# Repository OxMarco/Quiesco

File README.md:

<div align="center">

<picture>
  <source media="(prefers-color-scheme: dark)" srcset=".github/assets/banner-dark.svg">
  
</picture>

<br><br>

<br>

**[Build your own](#-build-your-own)** · **[Hardware](hardware/)** · **[Firmware](firmware/)** · **[App](app/)**

</div>

---

Quiesco is a pocket-sized monitor made for the room you sleep in. It measures
**CO₂, temperature, humidity, light and noise**, shows them on an e-ink screen
that reads from across the room, and syncs every night straight to your
phone. There is no Wi-Fi, no cloud and no account: your data stays yours.

Everything is open. This repository holds the PCB, the case, the firmware and
the companion app, so you can build one from scratch, reflash it from the
Arduino toolchain, or take it apart and make it your own.

Quiesco is a product of [Impossible Labs](https://impossiblelabs.xyz).

<picture>
  <source media="(prefers-color-scheme: dark)" srcset=".github/assets/screens-dark.svg">
  
</picture>

## Contents

- [Why Quiesco](#-why-quiesco)
- [What it measures](#-what-it-measures)
- [How it works](#-how-it-works)
- [Specs](#-specs)
- [Build your own](#-build-your-own)
- [Upgrade firmware](#-upgrade-firmware)
- [Repository map](#-repository-map)
- [Roadmap](#-roadmap)
- [The story behind it](#-the-story-behind-it)
- [Contributing](#-contributing)
- [Licence](#-licence)

## 🌙 Why Quiesco

Environmental monitors have boomed: Aranet, Airvalent and friends made CO₂
tracking friendly. But they are general-purpose. They watch the air, and
little else, against office standards.

Quiesco is built for the **bedroom**. Light and noise matter as much as CO₂ and
temperature for a good night, so it measures all of them and judges each one
against a comfort band. Every reading is **actionable**:

| When it says… | …you can |
|---|---|
| CO₂ is high | open a window or run ventilation |
| too warm, too cold | adjust heating, cooling or bedding |
| too dry, too damp | humidify or dehumidify |
| too much light | close the blinds or wear a sleep mask |
| too loud | check the insulation or reach for earplugs |

And unlike commercial devices, it is **completely open and unlocked**: it runs
the Arduino bootloader, so you can change the firmware with the Arduino IDE or
your favourite editor.

## 📊 What it measures

| Reading | Sensor | Comfortable | Warn | Bad |
|---|---|---|---|---|
| CO₂ | Sensirion **SCD41** (photoacoustic NDIR) | ≤ 800 ppm | 800–1000 ppm | > 1000 ppm |
| Temperature | Bosch **BME280** | 16–20 °C | 14–16 · 20–24 °C | < 14 · > 24 °C |
| Humidity | Bosch **BME280** | 40–60 % | 30–40 · 60–70 % | < 30 · > 70 % |
| Noise | Knowles **SPH0641LU4H-1** PDM mic, dB(A) Leq over ~7 s | ≤ 45 dB | 45–55 dB | > 55 dB |
| Light | Vishay **VEML7700** | informational | | |
| Pressure | Bosch **BME280** | informational; also compensates CO₂ | | |

The same bands drive the e-ink screen and the app, so the phone and the panel
always agree. The full policy is in [`firmware/UI.md`](firmware/UI.md#3-comfort-bands).

> [!IMPORTANT]
> Keep the unit out of direct sunlight. Sun on the case heats the sensors, so
> temperature reads several degrees high and humidity reads low. On a test
> bench, afternoon sun pushed the reading to 36 °C. A shaded bedside table or
> shelf, away from radiators and air vents, gives readings you can trust.

## ⚙ How it works

```mermaid
flowchart LR
    subgraph unit["Quiesco unit · nRF52840"]
        direction TB
        rail["Switched sensor rail"] --> sensors["SCD41 · BME280<br/>VEML7700 · PDM mic"]
        sensors --> cycle["Measurement cycle"]
        cycle --> flash[("8 MB flash<br/>sample log")]
        cycle --> eink["1.54″ e-ink<br/>Face · Ledger · Bento"]
        cycle --> ble["BLE service"]
        flash --> ble
    end
    ble <-- "authenticated, enrolled over USB" --> app["Companion app<br/>iOS · Android"]
    app --> db[("SQLite<br/>on your phone")]
```

Every interval (1, 5, 10 or 30 minutes; default **5 minutes**) the unit powers
up its sensor rail, measures everything, applies your calibration offsets,
appends the reading to its on-board log, redraws the e-ink panel only if the
picture changed, then powers the rail down and sleeps. A sensor that fails is
reported as unavailable, and the cycle carries on without it.

The app enrols with a unit while it is on USB power, using a six-digit code
shown on the panel. After that it sets the clock, downloads the log, charts
each night and lets you pick the screen or calibrate the sensors. One phone
can hold several units, each with its own name and sleep window.

## 📐 Specs

| | |
|---|---|
| **MCU** | Nordic nRF52840 on a Seeed XIAO nRF52840 Plus module, Arduino bootloader |
| **Connectivity** | Direct to the phone over the nRF52840's Bluetooth LE radio; only an enrolled phone can read data or change settings |
| **Sensors** | CO₂, temperature, humidity, pressure, light, noise |
| **Display** | GoodDisplay GDEW0154T8D, 1.54″ 152 × 152 e-ink, holds its image unpowered |
| **Storage** | Winbond W25Q64 8 MB SPI NOR flash (config + sample log) |
| **Power** | 3.7 V ~400 mAh LiPo (453035), USB-C charging, switched peripheral rail |
| **Expansion** | JST I²C and UART headers |
| **Case** | Two-part enclosure, MJF-printed in black PA12 nylon, four M3 screws ([why nylon](hardware/README.md#material)) |

## 🛠 Build your own

A Quiesco takes an afternoon to put together once the parts arrive. Each step
links to the folder with the details.

### What you need

- The **PCBA**: the board from [`hardware/`](hardware/), ordered assembled
- A **GDEW0154T8D** 1.54″ e-ink panel (24-pin FPC)
- A **3.7 V LiPo** that matches your board's battery connector: a ~400 mAh 453035
  (4.5 × 30 × 35 mm) with a **JST SH 1.0 2-pin** lead for the JST SH board, or
  the certified **EEMB LP402535-PCM-PTC-LD/-A22852** for the Minitek board (see
  [`hardware/`](hardware/README.md))
- A **3D-printed case** (MJF PA12 nylon, dyed black) and **4 × M3×10 socket-head screws**
- A USB-C cable, a Mac or Linux machine, and a phone with Bluetooth

### Steps

Start by cloning the repository:

```sh
git clone https://github.com/OxMarco/Quiesco.git
cd Quiesco
```

1. **Order the board** → [`hardware/`](hardware/README.md#order-the-board)
   Send the Gerbers, BOM and pick-and-place files to a PCB assembly service.
2. **Print the case** → [`hardware/`](hardware/README.md#print-the-case)
   The STL is ready to slice; STEP files are there if you want to modify it.
3. **Assemble** → [`hardware/`](hardware/README.md#assemble)
   Seat the display, plug in the battery, close the case.
4. **Test the unit** → [`TESTING.md`](TESTING.md)
   Copy the factory test onto the unit and check its screen says `PASS`.
5. **Flash the firmware** → [`firmware/`](firmware/README.md#quick-start)
   `make build`, then upload over USB.
6. **Install the app** → [`app/`](app/README.md#run-it)
   Build it onto your phone, plug the unit into USB and pair.

## ⬆ Upgrade firmware

No software needed, on macOS, Windows or Linux. Plug the unit into a
computer, tap **Settings → your unit → Update firmware** in the app, and a drive called
`XIAO-BOOT` appears. Copy `quiesco-X.Y.Z.uf2` onto it, and the unit restarts
with the new firmware. Settings, enrolled phones, calibration and history
are kept.

Troubleshooting, units without the app option, and making a release:
[`AGENT.md`](AGENT.md).

## 🗺 Repository map

| Folder | What's inside | Read this |
|---|---|---|
| [`hardware/`](hardware/) | Altium sources, schematic PDF, Gerbers, BOM, pick-and-place, case STL/STEP | [hardware/README.md](hardware/README.md) |
| [`firmware/`](firmware/) | Arduino C++ firmware for the nRF52840, test sketches, host tests and tools | [firmware/README.md](firmware/README.md) |
| [`app/`](app/) | Expo / React Native companion app for iOS and Android | [app/README.md](app/README.md) |
| [`landing/`](landing/) | The [quiesco.rest](https://quiesco.rest) website (Astro) | [landing/README.md](landing/README.md) |

Going deeper:

- [`firmware/HARDWARE.md`](firmware/HARDWARE.md): the board as the firmware sees it, pin map, traps and debugging
- [`firmware/SOFTWARE.md`](firmware/SOFTWARE.md): firmware architecture and features
- [`firmware/UI.md`](firmware/UI.md): the e-ink screens, pixel by pixel
- [`firmware/src/protocol/PROTOCOL.md`](firmware/src/protocol/PROTOCOL.md): the BLE contract between unit and app
- [`TESTING.md`](TESTING.md): testing each assembled unit, for builders and manufacturers
- [`TEST-PLAN.md`](TEST-PLAN.md): how the app and firmware are tested in code and CI
- [`AGENT.md`](AGENT.md): updating a unit's firmware (copy a file onto its USB drive)

## 🧭 Roadmap

- [x] PCB v1, assembled and tested
- [x] Measurement cycle with all sensors, calibration and CO₂ forced recalibration
- [x] E-ink screens: Face, Ledger and Bento
- [x] Persistent sample log on the on-board flash
- [x] BLE protocol with phone enrolment and authentication
- [x] Companion app: live reading, night charts, calibration
- [ ] BLE tested on air: iPhone and Mac done (2026-10-07), Android still to test
- [x] Firmware updates over USB, started from the app: copy one file, no software ([`AGENT.md`](AGENT.md))
- [ ] Measured power budget and battery life
- [x] App: more than one unit per phone, each with its own name and sleep window
- [ ] App on the App Store and Google Play
- [ ] Units for sale — *coming soon*
- [ ] Later: Quiesco XL, with PM2.5, PM10 and more sensors for fuller air-quality control, and a bigger screen

## 📖 The story behind it

<details>
<summary>Why I built Quiesco</summary>

<br>

Despite having studied electrical engineering and physics, I never had the
chance to work on electronics outside of university. My main job for the past
few years has been in fintech, mostly on software architecture. Yet I have
always wanted to launch my own product.

I own an Airvalent and a couple of Xiaomi environmental sensors and had a
chance to review the Aranet too, yet I felt these little devices could
definitely do more. That's why, in early 2026, I decided to dedicate part of my
free time to building Quiesco from the ground up.

The choice of sensors was tough. There are clear contenders on the market, but
most come with obvious drawbacks, like relying on the BME280's self-heating
element for the primary temperature reading, or gas sensors that draw too much
current for a rather generic value like VOC. So temperature, humidity and pressure
come from a BME280 on the switched rail, never self-heated, and the SCD41 is
used for CO₂ only.

**I wanted data that is actionable:** high CO₂ → ventilate; too much light →
wear a sleep mask; too much noise → check the acoustic insulation or use
earplugs.

</details>

## 🤝 Contributing

Issues and pull requests are welcome, from a typo to a new screen.

- **Firmware:** run `make verify` in `firmware/` before opening a PR; it checks
  the source policy and runs the host tests.
- **App:** run `npm test`, `npx tsc --noEmit` and `npx expo lint` in `app/`.
- **Protocol:** a change to the BLE contract touches both sides. Update
  [`PROTOCOL.md`](firmware/src/protocol/PROTOCOL.md), the firmware codec and
  the app's `src/protocol/` together; the golden vectors keep them honest.

## 🙏 Acknowledgements

Many thanks to the engineers at **PCBWay**, who helped tailor the PCB and the
enclosure to production standards.

## 📜 Licence

Quiesco is free and open source under the [GNU General Public License v3.0](LICENSE).
Third-party components are listed in
[`firmware/THIRD_PARTY_NOTICES.md`](firmware/THIRD_PARTY_NOTICES.md).

<div align="center">
<br>
<sub>Quiesco is a product of <a href="https://impossiblelabs.xyz">Impossible Labs</a> · <a href="https://quiesco.rest">quiesco.rest</a></sub>
</div>

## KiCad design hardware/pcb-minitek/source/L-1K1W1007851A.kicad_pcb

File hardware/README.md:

# Quiesco hardware

Everything you need to manufacture a Quiesco unit: the PCB **v1**
(`L-1K1W1007851A`) design and factory files, and the 3D-printable enclosure.

PCB v1 comes in two versions. They are the same board except for the battery
connector, J2. Each version has its own folder, and the two sets of files
must not be mixed.

| Version | Folder | J2, battery connector | Battery that plugs in | Design tool |
|---|---|---|---|---|
| **JST SH** | [`pcb-jst-sh/`](pcb-jst-sh/) | JST **SM02B-SRSS-TB**, SH 1.0 mm, 2-pin | any 453035-size LiPo with a JST SH 1.0 lead | Altium |
| **Minitek** | [`pcb-minitek/`](pcb-minitek/) | Amphenol **10144041-02011LF**, Minitek 0.8 mm, 2-pin | EEMB **LP402535-PCM-PTC-LD/-A22852**, IEC 62133-2 certified, used as supplied | KiCad |

In both versions J2 sits in the same place, pin 1 is VBAT and pin 2 is GND.

<table>
  <tr>
    <td align="center" width="50%"><br><sub><b>Top</b>: XIAO module, e-ink FPC, flash, SCD41, VEML7700, mic</sub></td>
    <td align="center" width="50%"><br><sub><b>Bottom</b></sub></td>
  </tr>
</table>

## Contents

- [The board at a glance](#the-board-at-a-glance)
- [Folder layout](#folder-layout)
- [Order the board](#order-the-board)
- [Parts not on the board](#parts-not-on-the-board)
- [Print the case](#print-the-case)
- [Assemble](#assemble)
- [Next: flash and test](#next-flash-and-test)

## The board at a glance

A two-layer PCB built around a **Seeed XIAO nRF52840 Plus** module, which
brings the MCU, Bluetooth radio, USB-C and LiPo charger. Every peripheral sits
on a **switched 3.3 V rail** that the firmware turns off between measurements.

| Ref | Part | Job |
|---|---|---|
| U3 | Seeed XIAO nRF52840 Plus | MCU, BLE, USB-C, LiPo charger |
| U6 | Sensirion SCD41-D-R1 | CO₂ (I²C `0x62`) |
| U2 | Bosch BME280 | temperature, humidity, pressure; pressure also compensates CO₂ (I²C `0x76`) |
| U5 | Vishay VEML7700 | ambient light (I²C `0x10`) |
| U4 | Knowles SPH0641LU4H-1 | PDM MEMS microphone |
| U1 | Winbond W25Q64JVSSIQ | 8 MB SPI NOR flash: config and sample log |
| J1 | 24-pin 0.5 mm FPC | GoodDisplay GDEW0154T8D e-ink panel |
| Q1 | AO3401 P-MOSFET | switched peripheral rail (`3V3ON`, active LOW) |
| Q2, L1, D1–D3 | SI1308EDL, 10 µH, MBR0530 | e-ink gate-voltage boost |
| J2 | 2-pin battery connector: JST SH 1.0 or Amphenol Minitek 0.8, depending on the [version](#quiesco-hardware) | battery |
| J3 / J4 | JST 4-pin | I²C and UART expansion |
| T1–T6 | test pads | SWDIO, SWCLK, VBUS, RESET, 3.3 V, GND |

The pin map, power sequencing, bus details and known quirks are documented
from the firmware's point of view in
[`firmware/HARDWARE.md`](../firmware/HARDWARE.md).

> [!IMPORTANT]
> The fitted module is the plain **Plus**, not the **Sense Plus**: v1 has no IMU,
> and the board's own external mic (U4) is the only microphone.

## Folder layout

```text
hardware/
├── pcb-jst-sh/                  PCB v1, J2 = JST SH 1.0 (SM02B-SRSS-TB)
│   ├── source/                  Altium project: .PrjPcb, .SchDoc, .PcbDoc
│   │   ├── schematic.pdf        schematic, printable
│   │   └── old/                 earlier schematic and BOM, for reference
│   ├── manufacturing/           what the factory needs
│   │   ├── gerbers/             Gerbers, drill files, IPC netlist
│   │   ├── bom.xlsx             bill of materials
│   │   ├── pick-and-place.csv   centroid file
│   │   └── process-spec.xlsx    fabrication settings
│   └── renders/                 top.png, bottom.png
├── pcb-minitek/                 PCB v1, J2 = Amphenol Minitek (10144041-02011LF)
│   ├── source/                  KiCad project: .kicad_pro, .kicad_sch, .kicad_pcb
│   └── manufacturing/
│       ├── gerbers/             Gerbers and drill files
│       ├── bom.xlsx             bill of materials
│       └── pick-and-place.csv   centroid file
└── case/                        enclosure, shared by both versions
    ├── v1/                      case-v1.stl (ready to slice), case-v1.step (editable)
    ├── v2/                      case-v2.stl, case-v2.step (in test)
    ├── assembly.step            full assembly with the PCBA
    ├── assembly-instructions.docx
    └── exploded.mp4             exploded-view animation
```

## Order the board

First pick the [version](#quiesco-hardware), then take every file from that
version's `manufacturing/` folder only.

1. **Zip the Gerbers.** Compress `manufacturing/gerbers/` into one archive and
   upload it as the PCB.
2. **Add assembly.** Upload `manufacturing/bom.xlsx` as the BOM and
   `manufacturing/pick-and-place.csv` as the centroid file. The BOM's
   **Substitution** column tells the factory which parts it may swap for an
   equivalent (passives, diodes, inductor) and which it must not (connectors,
   sensors, the XIAO module, the screen and the battery).
3. **Share the process spec.** `pcb-jst-sh/manufacturing/process-spec.xlsx`
   holds the fabrication settings used for the first boards, which PCBWay
   produced from the Altium outputs.
4. **Mind the not-fitted parts.** R1, R2, R3, R5, R6, R7, R8 and R9 are marked
   `NC` in the BOM and must stay empty: R1 would flip the microphone's
   channel, R7 is an unused rail bleeder, and the rest are per-sensor I²C
   pull-ups that the shared R14/R15 pair replaces.

## Parts not on the board

These ship loose and plug in during assembly (they are listed at the bottom of
the BOM):

| Part | Spec | Notes |
|---|---|---|
| E-ink panel | GoodDisplay **GDEW0154T8D**, 1.54″, 152 × 152, 24-pin 0.5 mm FPC | plugs into J1 |
| Battery, JST SH version | **3.7 V ~400 mAh** LiPo, **453035** size (4.5 × 30 × 35 mm), with a **JST SH 1.0 2-pin** lead, 10 cm, single-ended | plugs into J2. **Check polarity before plugging in** |
| Battery, Minitek version | EEMB **LP402535-PCM-PTC-LD/-A22852**: 3.7 V, 320 mAh typical, 37.0 × 25.5 × 4.3 mm max, with PCM and PTC fitted, 33 mm lead, Amphenol 10145492-02LF plug | plugs into J2 as supplied. Don't cut, crimp or extend the lead: any change voids the cell's IEC 62133-2 certificate |
| Screws | **4 × M3×10** hex socket head | close the case |

## Print the case

The enclosure is a two-part shell, about **53 × 53 × 15 mm**.

### Material

**MJF PA12 nylon, dyed black**, is the production material. Any MJF
service can print it; order both parts in PA12 with black dyeing.

The same files were printed in three processes to choose it
([build log with photos](https://hackaday.io/project/207079-quiesco/log/252495-choosing-a-case-material-abs-resin-or-mjf-nylon)):

| Process | Finish | Strength | Per case, 50 units | Verdict |
|---|---|---|---|---|
| FDM ABS | layer pattern on every face and in the screw counterbores | good | cheapest | prototypes only; some services can't print the 3.4 mm bezel |
| Black resin | smoothest, but shows every speck, scratch and fingerprint; standard black looks greyish and streaky | more brittle where the screws bite | ~$4 | no; Imagine Black is deeper but softens at 46 °C |
| **MJF PA12 nylon** | even matte black, fine grain that hides marks, clean vents | tough, screws thread in well | ~$5 | **chosen** |

Prices are JLC3DP online quotes from October 2026, before import VAT.

### Files

Both PCB versions fit the same case. The case pocket is about 38 × 30.5 mm,
with 8.5 mm above the board, so either battery fits.

- **Print** `case/v1/case-v1.stl` as-is.
- **Modify** `case/v1/case-v1.step` in your CAD tool, and use
  `case/assembly.step` to check clearances against the populated board.

**v2, in test.** `case/v2/case-v2.stl` and `case/v2/case-v2.step` rework the
vents and the light sensor opening. The display window and the board fit are
unchanged:

| Feature | v1 | v2 |
|---|---|---|
| Side vent | 6 slots, 1.5 mm wide, 1 mm fins | 5 slots, 1.8 mm wide, 1.6 mm fins, 45° pointed end (prints back-down without bridging) |
| Second vent | none | same 5 slots on the opposite wall, for cross-flow |
| Light sensor | 10.4 × 6.6 × 0.8 mm pocket for a clear insert | open 7.8 × 4.0 mm hole through the wall |
| Bezel outline | 50.3 mm, 0.1 mm clearance per side | 50.0 mm, 0.25 mm clearance per side |

Both versions have walls down to about 0.5 mm at the bezel corners and one
inner corner of the shell, below most print services' minimum. In MJF nylon
they print and hold up, but the 0.5 mm skin over each bezel screw hole
shows as a small dot on the front. A revision that leaves a 1.0 mm skin
(pilot holes 2.4 mm deep instead of 2.9 mm) and thickens the shell corner
is in progress. Use v1 until v2 has been tested.

If you change the window, re-measure how much of the panel it hides: the
screens leave a 7 px top inset for the v1 case (see
[`firmware/UI.md`](../firmware/UI.md#1-canvas)).

## Assemble

1. **Connect the display.** Open the J1 FPC latch, slide in the e-ink ribbon
   and close the latch. A badly seated ribbon shows up as missing rows in the
   factory test.
2. **Fit the battery.** Plug it into J2 and fix it in the lid, between
   the two ribs above the XIAO module, with double-sided tape.
3. **Seat the board in the lower shell.** Align the USB-C port with its
   opening first, then lower the board in.
4. **Close the case.** Make sure the microphone opening in the upper cover
   lines up with the hole on the PCBA, then drive in the four M3×10 screws.

## Next: flash and test

With the unit assembled, head to [`firmware/`](../firmware/README.md#test-a-new-unit)
to run the factory test sketch and flash the release firmware.

---

<sub>← Back to the [Quiesco overview](../README.md)</sub>

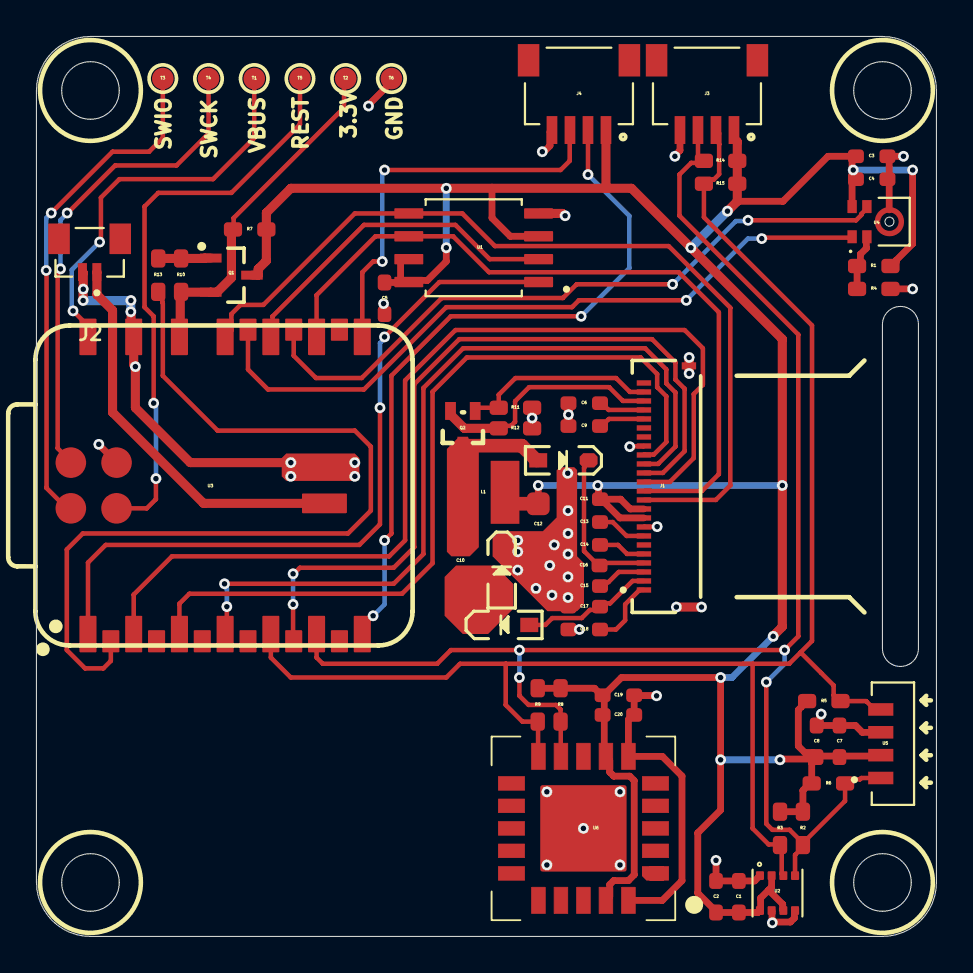
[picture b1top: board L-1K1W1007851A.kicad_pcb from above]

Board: 2 copper layers, 50.0 x 50.0 mm, 57 parts (0 on the bottom side), 37 nets.

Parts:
C1, C3, C5, C7, C19: 0.1uF/50V; C 0603
C2, C4, C8, C20: 10uF/10V; C 0603
C6, C9, C11, C13, C14, C15, C16, C17, C18: 1uF/50V; C 0603
C10, C12: 4.7uF/50V; C 0805
D1, D2, D3: MBR0530; SOD-323
J1: HC-FPC-05-09-24RLTAG; GCT_FFC2B28-24-G
J2: 10144041-02011LF; AMPHENOL_10144041-02011LF
J3, J4: SM04B-SRSS-TB(LF)(SN); JST_SM04B-SRSS-TB(LF)(SN)
L1: 10uH/1A; CD31
Q1: AO3401; SOT23-3N
Q2: SI1308EDL; SOT323
R1, R2, R3, R5, R6, R7, R8, R9: NC; R 0603
R4: 0R; R 0603
R10: 10K; R 0603
R11: 1M; R 0603
R12: 0.47R; R 0603
R13: 100R; R 0603
R14, R15: 4.7K; R 0603
T1, T2, T3, T4, T5, T6: PAD 1.2mm; TEST 1.2
U1: W25Q64JVSSIQ; SOIC127P790X216-8N
U2: BME280; PSON65P250X250X100-8N
U3: XIAO-nRF52840-Plus
U4: SPH0641LU4H-1; MIC_SPH0641LU4H-1
U5: VEML7700-TR; XDCR_VEML7700-TR
U6: SCD41-D-R1; SCD4x

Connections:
3V3ON: R13.2, U3.15
+3.3V: C1.2, C2.2, C3.2, C4.2, C5.2, C7.2, C8.2, C11.1, C12.2, C19.2, C20.2, J1.9, J1.10, J3.1, J4.1, L1.1, Q1.3, R1.1, R2.1, R3.1, R5.1, R6.1, R7.2, R8.1, R9.1, R14.1, R15.1, U1.3, U1.7, U1.8, U2.2, U2.6, U2.8, U4.5, U5.2, U6.7, U6.19
+3.3V_PS: Q1.2, R7.1, R10.1, T2.1, U3.12
BME_SCL: J3.3, R2.2, R6.2, R8.2, R14.2, U2.4, U3.6, U5.1, U6.9
BME_SDA: J3.2, R3.2, R5.2, R9.2, R15.2, U2.3, U3.5, U5.4, U6.10
C_RX: J4.3, U3.8
C_TX: J4.2, U3.7
ED_BUSY: J1.16, U3.3
ED_CS: J1.13, U3.2
ED_DC: J1.14, U3.19
ED_DI: J1.11, U1.5, U3.11
ED_RES: J1.15, U3.4
ED_SCLK: J1.12, U1.6, U3.9
GDR: J1.23, Q2.1, R11.1
GND: C1.1, C2.1, C3.1, C4.1, C5.1, C6.2, C7.1, C8.1, C9.2, C11.2, C12.1, C13.2, C14.2, C15.2, C16.1, C17.2, C18.2, C19.1, C20.1, D2.2, J1.8, J1.17, J1.S1, J1.S2, J2.2, J3.4, J4.4, R4.2, R11.2, R12.2, T6.1, U1.4, U2.1, U2.5, U2.7, U3.13, U3.27, U3.29, U4.3, U5.3, U6.6, U6.20, U6.21
NetC6_1: C6.1, J1.21
NetC9_1: C9.1, J1.20
NetC10_1: C10.1, D3.1, L1.2, Q2.3
NetC10_2: C10.2, D1.2, D2.1
NetC13_1: C13.1, J1.7
NetC14_1: C14.1, J1.5
NetC15_1: C15.1, J1.3
NetQ1_1: Q1.1, R10.2, R13.1
NetR1_2: R1.2, R4.1, U4.2
P0.02: U1.1, U3.1
P1.05: U3.22, U4.4
P1.07: U3.23, U4.1
P1.14: U1.2, U3.10
PREVGH: C16.2, D3.2, J1.4
PREVGL: C17.1, D1.1, J1.2
RESE: J1.22, Q2.2, R12.1
REST: T5.1, U3.26
SWDCLK: T4.1, U3.25
SWDIO: T3.1, U3.24
VBAT: J2.1, U3.28
VBUS: T1.1, U3.14
VCOM: C18.1, J1.1

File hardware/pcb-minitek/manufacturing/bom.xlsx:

Manufacturer | Comment | Mfg Part # | Designator | Footprint | LibRef | Quantity | Type
FOJAN(富捷) | 0.1uF/50V | FCC0603B104K500CT | C1, C3, C5, C7, C19 | C 0603 | CAP | 5
SAMSUNG(三星) | 10uF/10V | CL10A106MP8NNNC | C2, C4, C8, C20 | C 0603 | CAP | 4
HRE(芯声) | 1uF/50V | CGA0603X5R105K500JT | C6, C9, C11, C13, C14, C15, C16, C17, C18 | C 0603 | CAP | 9
SAMSUNG(三星) | 4.7uF/50V | CL21A475KBQNNNE | C10, C12 | C 0805 | CAP | 2
LRC(乐山无线电) | MBR0530 | LMBR0530ET1G | D1, D2, D3 | SOD-323HE | D 1N4148 | 3
GCT | HC-FPC-05-09-24RLTAG | FFC2B28-24-G | J1 | GCT_FFC2B28-24-G | FFC2B28-24-G | 1
Amphenol ICC | 10144041-02011LF | 10144041-02011LF | J2 | AMPHENOL_10144041-02011LF | AMPHENOL_10144041-02011LF | 1
JST | SM04B-SRSS-TB(LF)(SN) | SM04B-SRSS-TB(LF)(SN) | J3, J4 | JST_SM04B-SRSS-TB(LF)(SN) | SM04B-SRSS-TB(LF)(SN) | 2
YJYCOIN(益嘉源) | 10uH/1A | CD32YP0302-100M | L1 | CD31 | INDUCTOR | 1
HKT(合科泰) | AO3401 | AO3401 | Q1 | SOT23-3N | AO3401 | 1
TECH PUBLIC(台舟) | SI1308EDL | SI1308EDL | Q2 | SOT323 | AO3400 | 1
NC | NC | NC | R1, R2, R3, R5, R6, R7, R8, R9 | R 0603 | RES2 | 8
FOJAN(富捷) | 0R | FRC0603P000 TS | R4 | R 0603 | RES2 | 1
YAGEO(国巨) | 10K | RT0603BRD0710KL | R10 | R 0603 | RES2 | 1
UNI-ROYAL(厚声) | 1M | 0603WAF1004T5E | R11 | R 0603 | RES2 | 1
UNI-ROYAL(厚声) | 0.47R | CS03W5F470LT5E | R12 | R 0603 | RES2 | 1
UNI-ROYAL(厚声) | 100R | PS03W4F1000T5E | R13 | R 0603 | RES2 | 1
YAGEO(国巨) | 4.7K | RT0603BRD074K7L | R14, R15 | R 0603 | RES2 | 2
NC | PAD 1.2mm | NC | T1, T2, T3, T4, T5, T6 | TEST 1.2 | TEST | 6
Winbond(华邦) | W25Q64JVSSIQ | W25Q64JVSSIQ | U1 | SOIC127P790X216-8N | W25Q64BVSSIG | 1
Bosch(博世) | BME280 | BME280 | U2 | PSON65P250X250X100-8N | BME280 | 1
Seeed Studio | XIAO-nRF52840-Plus | 102010672 | U3 | XIAO-nRF52840-Plus | XIAO-nRF52840-Plus | 1
Knowles(楼氏) | SPH0641LU4H-1 | SPH0641LU4H-1 | U4 | MIC_SPH0641LU4H-1 | SPH0641LU4H-1 | 1
VISHAY(威世) | VEML7700-TR | VEML7700-TR | U5 | XDCR_VEML7700-TR | VEML7700-TR | 1
Sensirion(瑞士盛思锐) | SCD41-D-R1 | SCD41-D-R1 | U6 | SCD4x | SCD4x | 1
EEMB | 3.7V 320mAh, PCM+PTC, IEC 62133-2 | LP402535-PCM-PTC-LD/-A22852 | Battery | 37.0x25.5x4.3mm | Amphenol 10145492-02LF plug | 1
GooDisplay（佳显电子） | GDEW0154T8D | GDEW0154T8D | Screen | 1.54inch-0.5mmx24Pin | link | 1

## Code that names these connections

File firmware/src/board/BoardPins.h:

// SPDX-License-Identifier: GPL-3.0-only
#pragma once

#include <Arduino.h>

#if !defined(ARDUINO_SEEED_XIAO_NRF52840_PLUS) && \
    !defined(ARDUINO_SEEED_XIAO_NRF52840_SENSE_PLUS)
#error "Select board: XIAO nRF52840 (Sense) Plus - Seeed nRF52 mbed core"
#endif

namespace BoardPins {

// Arduino indices verified against the Seeeduino Mbed 2.9.3 Plus variants.
constexpr uint8_t kFlashCs = 0;       // W_NCS, P0.02
constexpr uint8_t kEpaperCs = 1;      // ED_CS, P0.03
constexpr uint8_t kEpaperBusy = 2;    // ED_BUSY, P0.28
constexpr uint8_t kEpaperReset = 3;   // ED_RES, P0.29
constexpr uint8_t kEpaperDc = 34;     // ED_DC, P0.10
constexpr uint8_t kPeripheralRail = 30;  // 3V3ON, P0.15, active low
constexpr uint8_t kBatteryEnable = 29;   // P0.14, active low
// BQ25101 ~CHG on the XIAO module itself (open drain, LOW = charging).
// VERIFY on hardware: module-level net, not on the carrier schematic.
constexpr uint8_t kChargeStatus = 22;    // ~CHG, P0.17

// Absolute nRF PSEL values, not Arduino indices.
constexpr uint32_t kPdmClockPsel = 37;  // P1.05
constexpr uint32_t kPdmDataPsel = 39;   // P1.07
// The battery ADC channel is not named here: BatteryMonitor selects it through
// the SAADC's own AnalogInput7 register field (P0.31), so a constant here would
// be a second source of truth that nothing enforces.

// Wire and SPI must use the core-provided instances. Their variant mappings
// are verified; duplicating their numeric pins here would invite misuse.
// The one exception: I2cBusRecovery clocks a stuck bus by hand before
// Wire.begin(), so it needs the raw port pins (SDA P0.04, SCL P0.05, as the
// smoke sketch's bit-bang probe uses them).
constexpr uint32_t kI2cSdaPortPin = 4;
constexpr uint32_t kI2cSclPortPin = 5;

static_assert(D0 == kFlashCs, "Unexpected D0 mapping in selected board core");
static_assert(D1 == kEpaperCs, "Unexpected D1 mapping in selected board core");
static_assert(D11 == kPeripheralRail,
              "Unexpected D11 mapping in selected board core");
static_assert(D15 == kEpaperDc,
              "Unexpected D15 mapping in selected board core");
static_assert(PIN_VBAT_ENABLE == kBatteryEnable,
              "Unexpected battery-enable mapping in selected board core");

}  // namespace BoardPins

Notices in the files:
README.md:
Licence: GPL v3
